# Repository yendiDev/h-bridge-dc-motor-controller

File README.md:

# H-Bridge DC Motor Controller

To be able to control a DC motor in varying speed and direction, an h-brige motor controller is essential. This pcb design uses PMOS and NMOS field-effect transistors to control the direction of current flowing to a DC motor, allowing for it to be controlled in different ways using a microcontroller.

It also includes opto-electronic oscillators for ensuring voltage spikes and unforseen current draws from rather noisy DC motors do not affect a microcontroller connected to it. It makes available screw terminals for connecting.

Below are screenshots of the PCB:

### Schematics:

### PCB Layout:
Front layer:

Bottom layer:

### 3D view of PCB:

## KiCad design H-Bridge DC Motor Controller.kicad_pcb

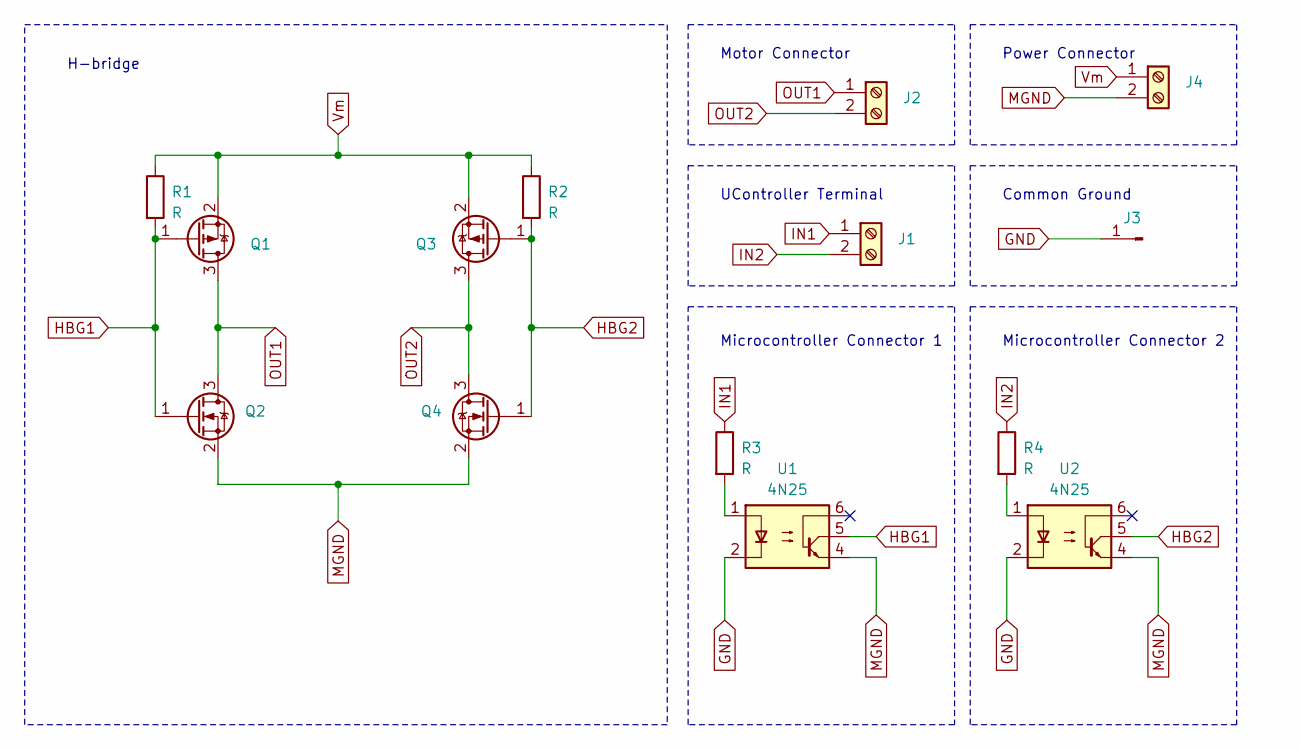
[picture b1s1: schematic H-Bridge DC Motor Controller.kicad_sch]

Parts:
J1, J2: Screw_Terminal_01x02; TerminalBlock_Phoenix_MKDS-1,5-2_1x02_P5.00mm_Horizontal
J3: Conn_01x01_Pin; PinHeader_1x01_P2.54mm_Vertical
J4: Screw_Terminal_01x02; TerminalBlock_Phoenix_MKDS-1,5-2-5.08_1x02_P5.08mm_Horizont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
Q1, Q3: AO3401A; SOT-23
Q2, Q4: IRLML0030; SOT-23
R1, R2, R3, R4: R; R_Axial_DIN0204_L3.6mm_D1.6mm_P5.08mm_Horizontal
U1, U2: 4N25; DIP-6_W7.62mm

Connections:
GND: J3.1, U1.2, U2.2
HBG1: Q1.1 (G), Q2.1 (G), R1.2, U1.5
HBG2: Q3.1 (G), Q4.1 (G), R2.2, U2.5
IN1: J1.1, R3.1
IN2: J1.2, R4.1
MGND: J4.2, Q2.2 (S), Q4.2 (S), U1.4, U2.4
unnamed: R3.2, U1.1
unnamed: R4.2, U2.1
OUT1: J2.1, Q1.3 (D), Q2.3 (D); also elsewhere on the board
OUT2: J2.2, Q3.3 (D), Q4.3 (D); also elsewhere on the board
Vm: J4.1, Q1.2 (S), Q3.2 (S), R1.1, R2.1

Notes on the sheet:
Motor Connector
UController Terminal
Microcontroller Connector 1
Common Ground
H-bridge
Power Connector
Microcontroller Connector 2

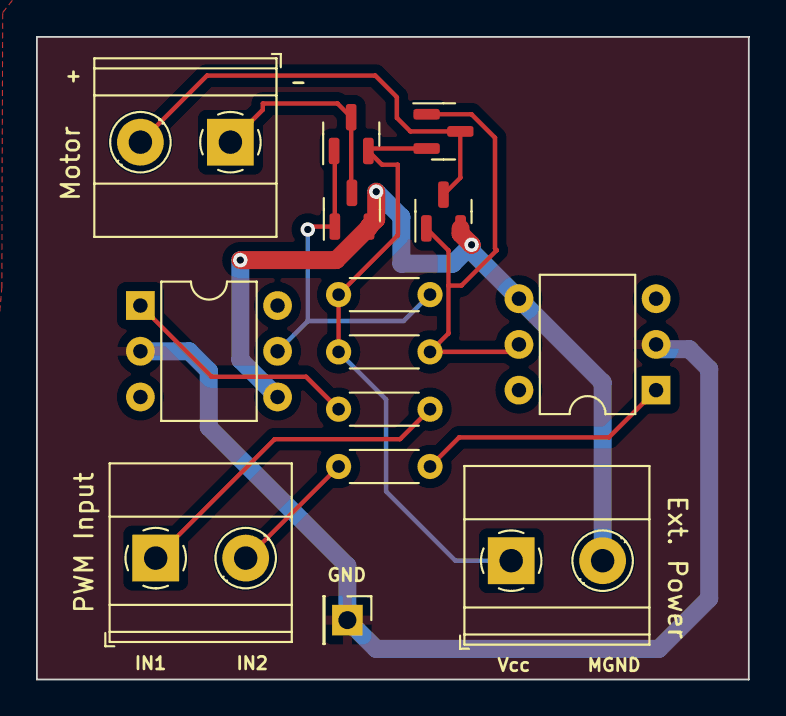
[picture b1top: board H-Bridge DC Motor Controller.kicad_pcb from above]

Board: 2 copper layers, 39.6 x 35.7 mm, 14 parts (0 on the bottom side), 11 nets.

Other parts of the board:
JE: Screw_Terminal_01x02; TerminalBlock_Phoenix_MKDS-1,5-2_1x02_P5.00mm_Horizontal

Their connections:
OUT1: JE.1; also elsewhere on the board
OUT2: JE.2; also elsewhere on the board
